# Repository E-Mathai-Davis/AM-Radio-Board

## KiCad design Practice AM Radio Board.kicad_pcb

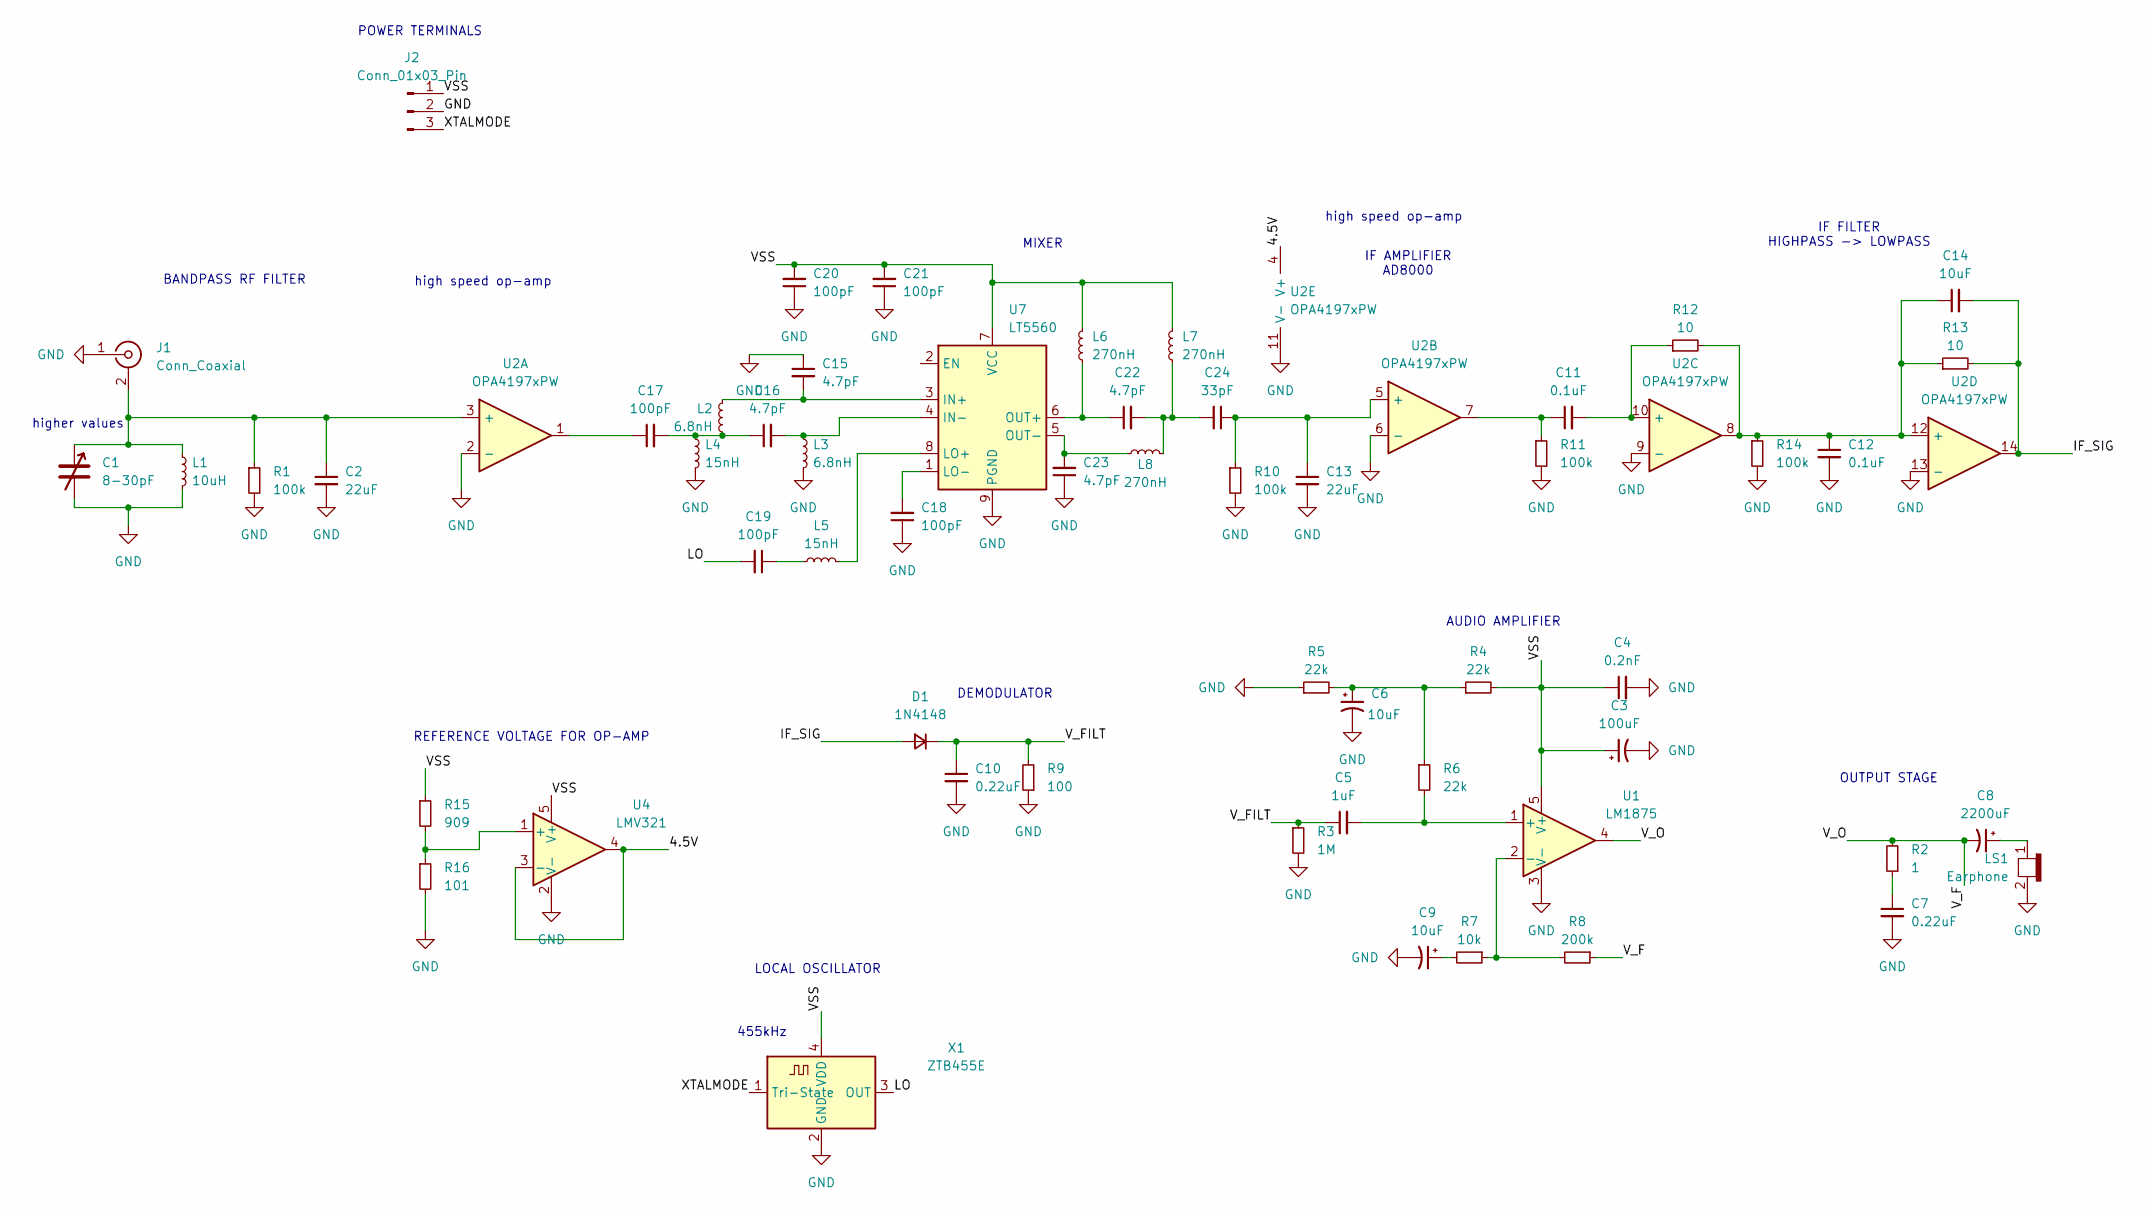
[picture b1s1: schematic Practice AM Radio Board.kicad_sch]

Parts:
C1: 8-30pF; CP_Elec_4x3.9
C2, C13: 22uF; Yu-C_0402_mil
C3: 100uF; C_Elec_10x10.2
C4: 0.2nF; C_0603_1608Metric
C5: 1uF; Yu-C_0402_mil
C6, C9: 10uF; CAP_B6-SVPK_PAN-M
C7, C10: 0.22uF; C_0603_1608Metric
C8: 2200uF; Cap_Elec_10.4x10.4
C11, C12: 0.1uF; Yu-C_0402_mil
C14: 10uF; Yu-C_0402_mil
C15, C16, C22, C23: 4.7pF; Yu-C_0402_mil
C17, C18, C19, C20, C21: 100pF; Yu-C_0402_mil
C24: 33pF; Yu-C_0402_mil
D1: 1N4148; Yu-D_SOD-123
J1: Conn_Coaxial; SMA_Molex_73251-1153_EdgeMount_Horizontal
J2: Conn_01x03_Pin; PinHeader_1x03_P2.54mm_Vertical
L1: 10uH; Yu-L_0603_mil
L2, L3: 6.8nH; Yu-L_0603_mil
L4, L5: 15nH; Yu-L_0603_mil
L6, L7, L8: 270nH; Yu-L_0603_mil
LS1: Earphone; MagneticBuzzer_ProSignal_ABT-410-RC
R1, R10, R11, R14: 100k; R_0402_1005Metric
R2: 1; R_0805_2012Metric
R3: 1M; Yu-R_0402_mil
R4, R5, R6: 22k; Yu-R_0402_mil
R7: 10k; Yu-R_0402_mil
R8: 200k; Yu-R_0402_mil
R9: 100; R_0805_2012Metric
R12, R13: 10; R_0402_1005Metric
R15: 909; R_0402_1005Metric
R16: 101; R_0402_1005Metric
U1: LM1875; TO-220-5_P3.4x3.7mm_StaggerOdd_Lead3.8mm_Vertical
U2: OPA4197xPW; TSSOP-14_4.4x5mm_P0.65mm
U4: LMV321; Yu-SOT-23-5
U7: LT5560; DFN-8-1EP_3x3mm_P0.5mm_EP1.66x2.38mm
X1: ZTB455E; Oscillator_SMD_ECS_2520MV-xxx-xx-4Pin_2.5x2.0mm

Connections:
/4.5V: U2.4 (V+), U4.3 (-), U4.4
/IF_SIG: C14.2, D1.2 (A), R13.2, U2.14
/LO: C19.2, X1.3 (OUT)
/VSS: C3.1, C4.1, C20.2, C21.2, J2.1, L6.2, L7.2, R4.2, R15.1, U1.5 (V+), U4.5 (V+), U7.7 (VCC), X1.4 (VDD)
/V_F: C8.2, R2.2, R8.1, U1.4
/V_FILT: C5.1, C10.1, D1.1 (K), R3.1, R9.2
/XTALMODE: J2.3, X1.1 (Tri-State)
GND: C1.2, C2.2, C3.2, C4.2, C6.2, C7.2, C9.2, C10.2, C12.2, C13.2, C15.1, C18.1, C20.1, C21.1, C23.1, J1.1 (In), J2.2, L1.2, L3.2, L4.2, LS1.2 (+), R1.2, R3.2, R5.1, R9.1, R10.2, R11.2, R14.2, R16.2, U1.3 (V-), U2.2 (-), U2.6 (-), U2.9 (-), U2.11 (V-), U2.13 (-), U4.2 (V-), U7.9 (PGND), X1.2 (GND)
unnamed: C6.1, R4.1, R5.2, R6.1
unnamed: C7.1, R2.1
unnamed: C9.1, R7.2
unnamed: C11.1, R11.1, U2.7
unnamed: C16.1, C17.2, L2.2, L4.1
unnamed: C17.1, U2.1
unnamed: C19.1, L5.1
unnamed: C22.2, C24.2, L7.1, L8.2
unnamed: C1.1, C2.1, J1.2 (Ext), L1.1, R1.1, U2.3 (+)
unnamed: C8.1, LS1.1 (-)
unnamed: C5.2, R6.2, U1.1 (+)
unnamed: R7.1, R8.2, U1.2 (-)
unnamed: C13.1, C24.1, R10.1, U2.5 (+)
unnamed: C11.2, R12.1, U2.10 (+)
unnamed: C12.1, C14.1, R12.2, R13.1, R14.1, U2.8, U2.12 (+)
unnamed: R15.2, R16.1, U4.1 (+)
unnamed: C15.2, L2.1, U7.3 (IN+)
unnamed: C16.2, L3.1, U7.4 (IN-)
unnamed: L5.2, U7.8 (LO+)
unnamed: C18.2, U7.1 (LO-)
unnamed: C22.1, L6.1, U7.6 (OUT+)
unnamed: C23.2, L8.1, U7.5 (OUT-)

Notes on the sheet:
MIXER
POWER TERMINALS
higher values
AUDIO AMPLIFIER
high speed op-amp
IF FILTER HIGHPASS -> LOWPASS
455kHz
REFERENCE VOLTAGE FOR OP-AMP
BANDPASS RF FILTER
OUTPUT STAGE
LOCAL OSCILLATOR
DEMODULATOR
IF AMPLIFIER AD8000

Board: 2 copper layers, 57 parts (0 on the bottom side), 30 nets, no tracks yet.
